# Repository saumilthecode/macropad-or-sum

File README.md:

# sharkpad

Board outline graciously yoinked from blahaj.sg

Essentially 6 keys & a vibration motor(imagine everytime it sensed a error it would start schizoing out)

The PCB looksl like this

the schematic is this

overall sharkpad should look like this

PCB sits on top of the bottom case with everything rounded off for comfort. the yellow is to be printed seperately and slotted in on top (it is cut off on the tail & xiao end so that there's no clearance issues + easy access + so the vibration motor can free itself when the time comes

document with all sides of the finished pad!

Bom

6x Cherry MX Switches

6x Keycaps (self owned)

1x XIAO RP2040

1x Case (1 printed part)

2x SK6812MINI (LED's)

1x[ Adafruit #1201 ](https://www.adafruit.com/product/1201?srsltid=AfmBOorIg7DYS5Oe22-k5PqfDXi-HshCgHwpwxbLdSgYLjnJjXQLFYlo)

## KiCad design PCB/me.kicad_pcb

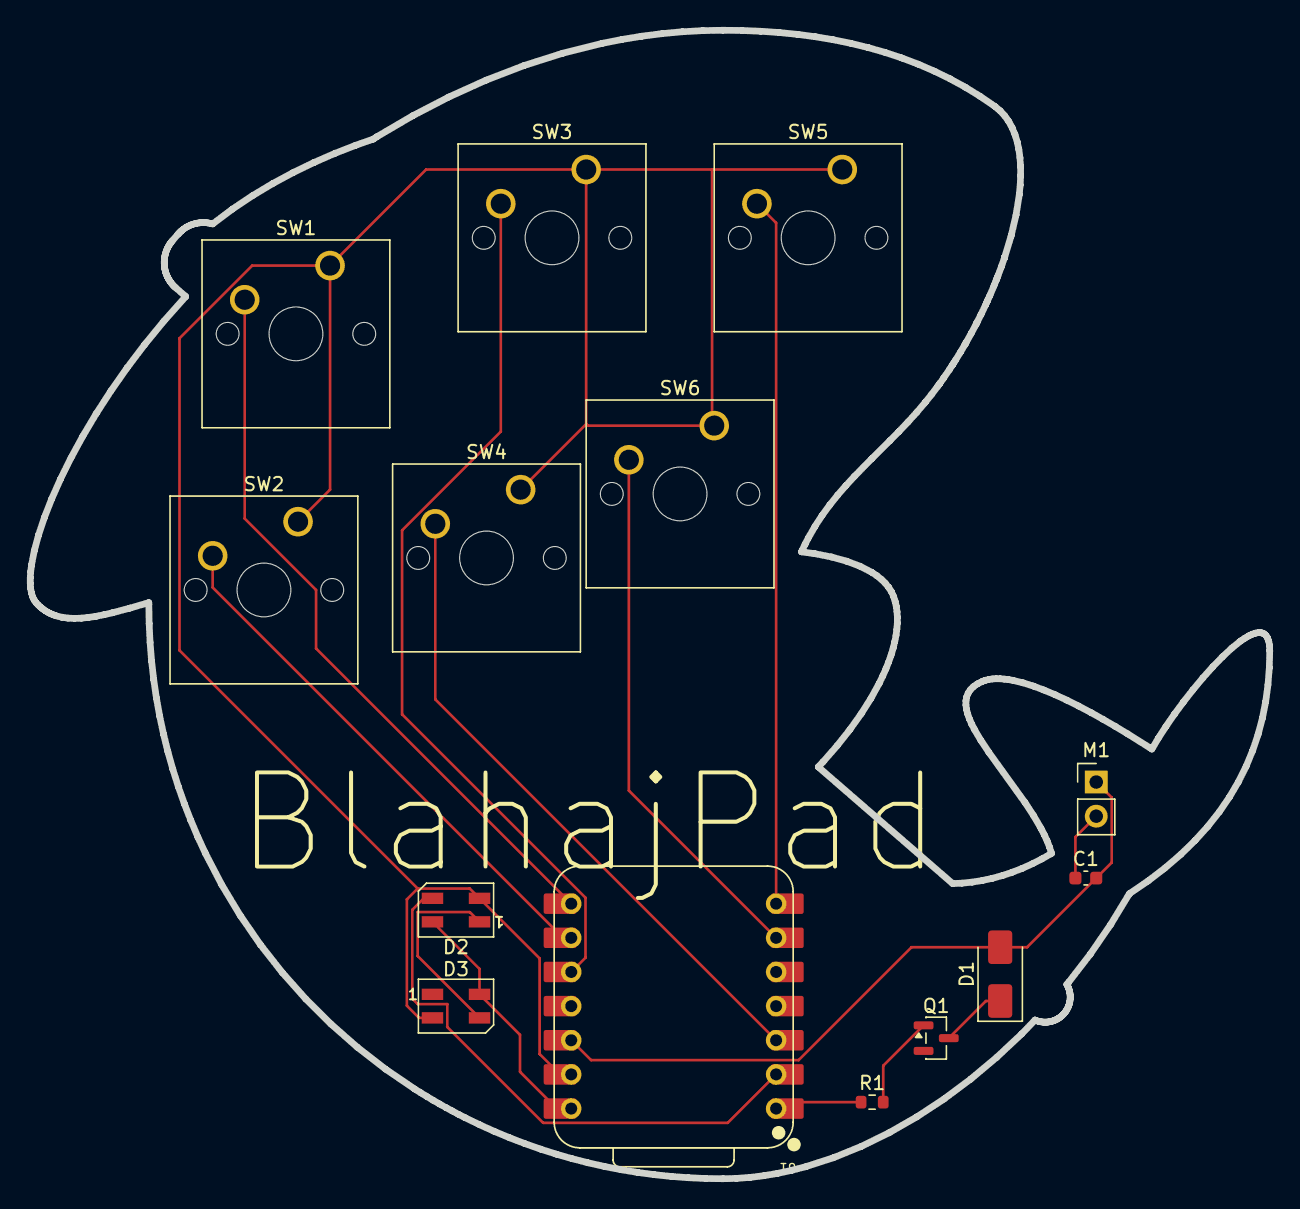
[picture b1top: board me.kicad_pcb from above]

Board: 2 copper layers, 92.2 x 85.4 mm, 14 parts (0 on the bottom side), 14 nets.

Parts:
C1: 100 nF; C_0603_1608Metric
D1: SS14; D_SMA
D2, D3: SK6812MINI; LED_SK6812MINI_PLCC4_3.5x3.5mm_P1.75mm
M1: Motor_DC; PinHeader_1x02_P2.54mm_Vertical
Q1: AO3400A; SOT-23
R1: 100 ohm; R_0603_1608Metric
SW1, SW2, SW3, SW4, SW5, SW6: SW_Push; SW_Cherry_MX_1.00u_PCB
U1: XIAO-RP2040-DIP

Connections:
+3.3V: C1.2, D1.2 (A), M1.1 (+), U1.12 (3V3)
+5V: D2.4 (VDD), D3.4 (VDD), U1.14 (VBUS)
GND: D2.2 (VSS), D3.2 (VSS), Q1.2 (S), SW1.1, SW2.1, SW3.1, SW4.1, SW5.1, SW6.1, U1.13 (GND)
unnamed: C1.1, D1.1 (K), M1.2 (-), Q1.3 (D)
unnamed: D2.3 (DIN), U1.2 (GPIO27/ADC1/A1)
unnamed: D2.1 (DOUT), D3.3 (DIN)
unnamed: Q1.1 (G), R1.2
unnamed: SW5.2, U1.7 (GPIO0/TX)
unnamed: SW1.2, U1.8 (GPIO1/RX)
unnamed: SW2.2, U1.9 (GPIO2/SCK)
unnamed: SW3.2, U1.10 (GPIO4/MISO)
unnamed: SW6.2, U1.6 (GPIO7/SCL)
unnamed: R1.1, U1.1 (GPIO26/ADC0/A0)
unnamed: SW4.2, U1.3 (GPIO28/ADC2/A2)

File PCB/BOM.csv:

"Reference","Qty","Value","DNP","Exclude from BOM","Exclude from Board","Footprint","Datasheet"
"C1","1","100 nF","","","","Capacitor_SMD:C_0603_1608Metric","~"
"D1","1","SS14","","","","Diode_SMD:D_SMA","https://www.vishay.com/docs/88746/ss12.pdf"
"D2,D3","2","SK6812MINI","","","","LED_SMD:LED_SK6812MINI_PLCC4_3.5x3.5mm_P1.75mm","https://cdn-shop.adafruit.com/product-files/2686/SK6812MINI_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"
"M1","1","Motor_DC","","","","Connector_PinHeader_2.54mm:PinHeader_1x02_P2.54mm_Vertical","~"
"Q1","1","AO3400A","","","","Package_TO_SOT_SMD:SOT-23","http://www.aosmd.com/pdfs/datasheet/AO3400A.pdf"
"R1","1","100 ohm","","","","Resistor_SMD:R_0603_1608Metric","~"
"SW1,SW2,SW3,SW4,SW5,SW6","6","SW_Push","","","","Button_Switch_Keyboard:SW_Cherry_MX_1.00u_PCB","~"
"U1","1","XIAO-RP2040-DIP","","","","Seeed Studio XIAO Series Library:XIAO-RP2040-DIP",""

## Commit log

2025-11-11 erwovnojerwnhvonwejvew
    wrjgvwjngvloekr3w
2025-11-12 aiehf
2025-11-12 houweg
2025-11-12 wioehgu
2025-11-12 please
2025-11-12 beforeitbreaks
2025-11-12 wueh
2025-11-12 firmware
2025-11-12 finally
2025-11-13 weug
2025-11-13 wouhger
2025-11-13 readme
2025-11-13 ewgih
2025-11-16 [ImgBot] Optimize images
    *Total -- 11,432.67kb -> 7,925.92kb (30.67%)
    /pictures/schematic.png -- 241.75kb -> 64.15kb (73.47%)
    /pictures/pcb screenshot.png -- 286.04kb -> 125.58kb (56.1%)
    /PCB/OPL_Kicad_Library-master/images/XIAO_Family_1.png -- 183.95kb -> 89.84kb (51.16%)
    /PCB/OPL_Kicad_Library-master/Grove Vision AI V2 Library/2.png -- 34.09kb -> 16.89kb (50.45%)
    /PCB/OPL_Kicad_Library-master/images/15.png -- 264.54kb -> 162.09kb (38.73%)
2025-11-19 uohewf
2025-11-19 i hate this
2025-11-19 everything's smaller now
2025-11-19 turns out im sped
2025-11-19 i hate everything
2025-12-04 delete
